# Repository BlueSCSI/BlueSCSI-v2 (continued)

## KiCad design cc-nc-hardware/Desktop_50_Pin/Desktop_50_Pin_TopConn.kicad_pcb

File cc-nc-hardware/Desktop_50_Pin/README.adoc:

BlueSCSI V2 Desktop 50 Pin
© 2022 - 2023 Tech by Androda, LLC

.All files in this cc-nc-hardware folder (and subfolders) are licensed CC BY-NC-SA 4.0:
* https://creativecommons.org/licenses/by-nc-sa/4.0/legalcode[Creative Commons Attribution-NonCommercial-ShareAlike 4.0 International Public License]

.The Dekstop 50 Pin hardware design contains one element which is © SnapEDA, as follows:
* SM04B-SRSS-TB(LF)(SN) Symbol And Footprint Copyright SnapEDA
* https://www.snapeda.com/parts/SM04B-SRSS-TB%28LF%29%28SN%29/JST%20Sales/view-part/
* License For This Symbol and Footprint Only: CC-BY-SA 4.0
* https://creativecommons.org/licenses/by-sa/4.0/
* This license contains a warranty disclaimer, please read it in full

.Translations of the CC BY-NC-SA 4.0 license are available, in a variety of languages:
* https://creativecommons.org/licenses/by-nc-sa/4.0/legalcode.fr[français]
* https://creativecommons.org/licenses/by-nc-sa/4.0/legalcode.ja[日本語]
* https://creativecommons.org/licenses/by-nc-sa/4.0/legalcode.pl[polski]
* https://creativecommons.org/licenses/by-nc-sa/4.0/legalcode.zh-Hans[中文]

.Explanations of the various rights afforded by this CC BY-NC-SA 4.0 license are also available in many languages:
* https://creativecommons.org/licenses/by-nc-sa/4.0/[English]
* https://creativecommons.org/licenses/by-nc-sa/4.0/deed.fr[français]
* https://creativecommons.org/licenses/by-nc-sa/4.0/deed.ja[日本語]
* https://creativecommons.org/licenses/by-nc-sa/4.0/deed.pl[polski]
* https://creativecommons.org/licenses/by-nc-sa/4.0/deed.zh[中文]

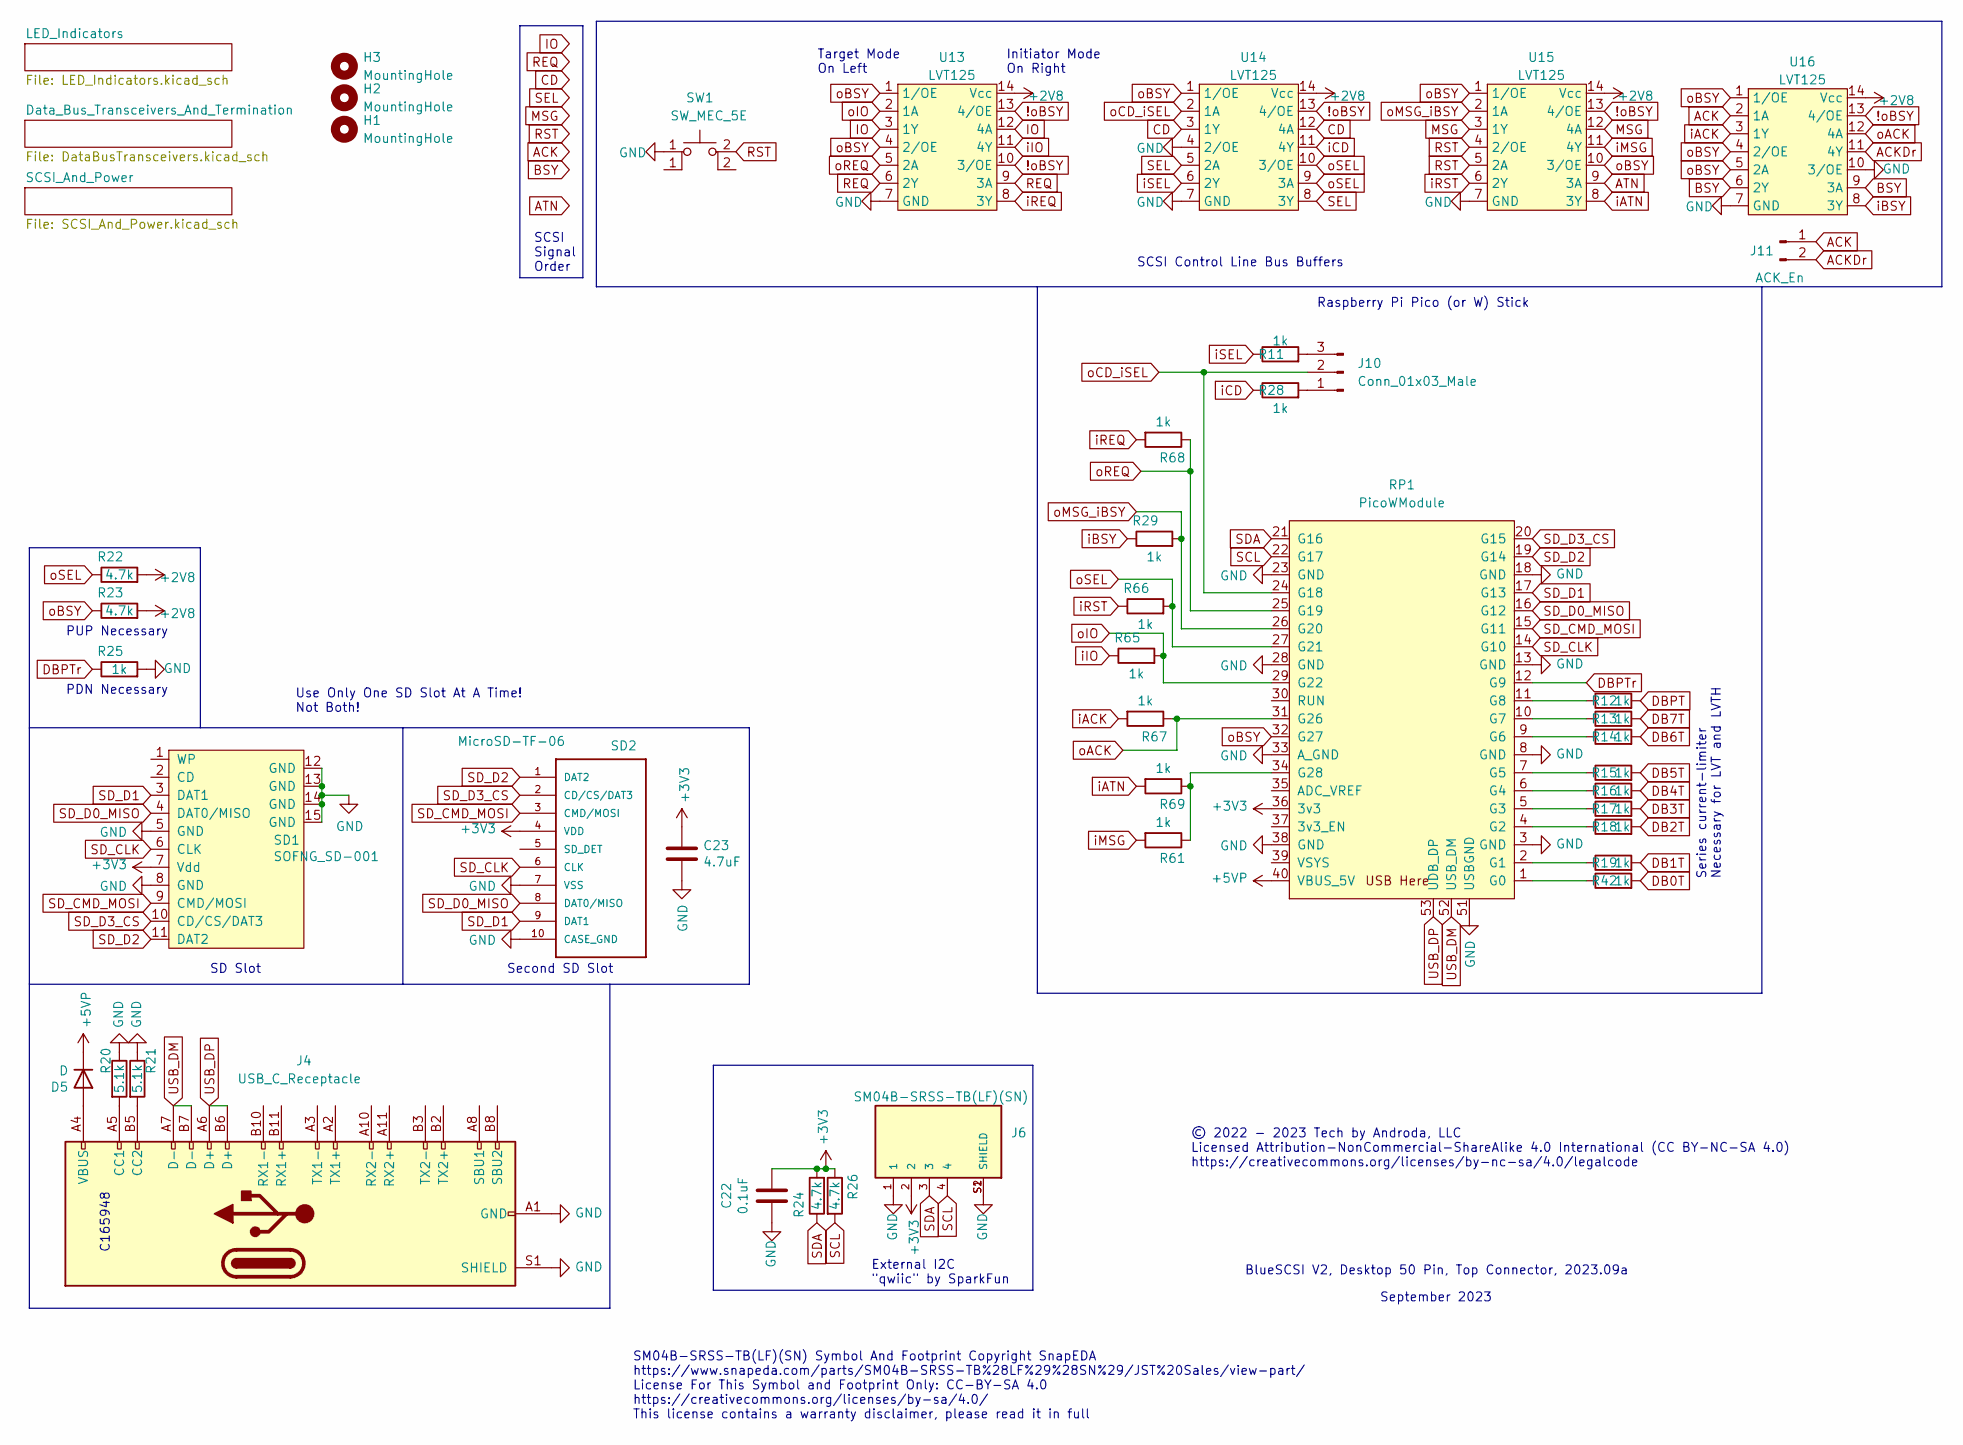
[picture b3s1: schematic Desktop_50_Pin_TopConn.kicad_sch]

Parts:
C22: 0.1uF; C_0805_2012Metric_Pad1.18x1.45mm_HandSolder
C23: 4.7uF; C_0805_2012Metric_Pad1.18x1.45mm_HandSolder
D5: D; D_SMA
H1, H2, H3: MountingHole; MountingHole_3.2mm_M3
J4: USB_C_Receptacle; USB_C_Receptacle_HRO_TYPE-C-31-M-12
J6: SM04B-SRSS-TB(LF)(SN); JST_SM04B-SRSS-TB(LF)(SN)
J10: Conn_01x03_Male; PinHeader_1x03_P2.54mm_Vertical
J11: ACK_En; PinHeader_1x02_P2.54mm_Vertical
R11, R25, R28, R29, R61, R65, R66, R67, R68, R69: 1k; R_0402_1005Metric
R12, R13, R14, R15, R16, R17, R18, R19, R42: 1k; R_0402_1005Metric_Pad0.72x0.64mm_HandSolder
R20, R21: 5.1k; R_0402_1005Metric
R22, R23, R24, R26: 4.7k; R_0603_1608Metric
RP1: PicoWModule; Raspberry_Pi_PicoW_SMT_THT
SD1: SOFNG_SD-001
SD2: MicroSD-TF-06; TF-06_MicroSD; MANUFACTURER_PART_NUMBER C693844
SW1: SW_MEC_5E; TS-1187A-B-A-B
U13, U14, U15, U16: LVT125; TSSOP-14_4.4x5mm_P0.65mm

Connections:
!oBSY: U13.10 (3/OE), U13.13 (4/OE), U14.13 (4/OE), U15.13 (4/OE), U16.13 (4/OE); also elsewhere on the board
+2V8: R22.2, R23.2, U13.14 (Vcc), U14.14 (Vcc), U15.14 (Vcc), U16.14 (Vcc); also elsewhere on the board
ACK: J11.1, U16.2 (1A); also elsewhere on the board
ACKDr: J11.2, U16.11 (4Y)
ATN: U15.9 (3A); also elsewhere on the board
BSY: U16.6 (2Y), U16.9 (3A); also elsewhere on the board
CD: U14.3 (1Y), U14.12 (4A); also elsewhere on the board
DB0T: R42.2; also elsewhere on the board
DB1T: R19.2; also elsewhere on the board
DB2T: R18.2; also elsewhere on the board
DB3T: R17.2; also elsewhere on the board
DB4T: R16.2; also elsewhere on the board
DB5T: R15.2; also elsewhere on the board
DB6T: R14.2; also elsewhere on the board
DB7T: R13.2; also elsewhere on the board
DBPT: R12.2; also elsewhere on the board
DBPTr: R25.1, RP1.12 (G9); also elsewhere on the board
GND: C22.1, C23.2, J4.A1 (GND), J4.A12 (GND), J4.B1 (GND), J4.B12 (GND), J4.S1 (SHIELD), J6.1, J6.S1 (SHIELD), J6.S2 (SHIELD), R20.1, R21.1, R25.2, RP1.3 (GND), RP1.8 (GND), RP1.13 (GND), RP1.18 (GND), RP1.23 (GND), RP1.28 (GND), RP1.33 (A_GND), RP1.38 (GND), RP1.51 (USBGND), SD1.5 (GND), SD1.8 (GND), SD1.12 (GND), SD1.13 (GND), SD1.14 (GND), SD1.15 (GND), SD2.7 (VSS), SD2.10 (CASE_GND), SW1.1, U13.7 (GND), U14.4 (2/OE), U14.7 (GND), U15.7 (GND), U16.7 (GND), U16.10 (3/OE); also elsewhere on the board
IO: U13.3 (1Y), U13.12 (4A); also elsewhere on the board
MSG: U15.3 (1Y), U15.12 (4A); also elsewhere on the board
unnamed: D5.2 (A), J4.A4 (VBUS), J4.A9 (VBUS), J4.B4 (VBUS), J4.B9 (VBUS)
unnamed: J4.A5 (CC1), R20.2
unnamed: J4.B5 (CC2), R21.2
unnamed: J10.1, R28.2
unnamed: J10.3, R11.2
unnamed: R12.1, RP1.11 (G8)
unnamed: R13.1, RP1.10 (G7)
unnamed: R14.1, RP1.9 (G6)
unnamed: R15.1, RP1.7 (G5)
unnamed: R16.1, RP1.6 (G4)
unnamed: R17.1, RP1.5 (G3)
unnamed: R18.1, RP1.4 (G2)
unnamed: R19.1, RP1.2 (G1)
unnamed: R42.1, RP1.1 (G0)
unnamed: R61.1, R69.1, RP1.34 (G28)
REQ: U13.6 (2Y), U13.9 (3A); also elsewhere on the board
RST: SW1.2 (A), U15.4 (2/OE), U15.5 (2A); also elsewhere on the board
SCL: J6.4, R26.2, RP1.22 (G17)
SDA: J6.3, R24.1, RP1.21 (G16)
SD_CLK: RP1.14 (G10), SD1.6 (CLK), SD2.6 (CLK)
SD_CMD_MOSI: RP1.15 (G11), SD1.9 (CMD/MOSI), SD2.3 (CMD/MOSI)
SD_D0_MISO: RP1.16 (G12), SD1.4 (DAT0/MISO), SD2.8 (DAT0/MISO)
SD_D1: RP1.17 (G13), SD1.3 (DAT1), SD2.9 (DAT1)
SD_D2: RP1.19 (G14), SD1.11 (DAT2), SD2.1 (DAT2)
SD_D3_CS: RP1.20 (G15), SD1.10 (CD/CS/DAT3), SD2.2 (CD/CS/DAT3)
SEL: U14.5 (2A), U14.8 (3Y); also elsewhere on the board
USB_DM: J4.A7 (D-), J4.B7 (D-), RP1.52 (USB_DM)
USB_DP: J4.A6 (D+), J4.B6 (D+), RP1.53 (UDB_DP)
iACK: R67.2, U16.3 (1Y)
iATN: R69.2, U15.8 (3Y)
iBSY: R29.1, U16.8 (3Y)
iCD: R28.1, U14.11 (4Y)
iIO: R65.1, U13.11 (4Y)
iMSG: R61.2, U15.11 (4Y)
iREQ: R68.2, U13.8 (3Y)
iRST: R66.1, U15.6 (2Y)
iSEL: R11.1, U14.6 (2Y)
oACK: R67.1, RP1.31 (G26), U16.12 (4A)
oBSY: R23.1, RP1.32 (G27), U13.1 (1/OE), U13.4 (2/OE), U14.1 (1/OE), U15.1 (1/OE), U15.10 (3/OE), U16.1 (1/OE), U16.4 (2/OE), U16.5 (2A); also elsewhere on the board
oCD_iSEL: J10.2, RP1.24 (G18), U14.2 (1A)
oIO: R65.2, RP1.29 (G22), U13.2 (1A)
oMSG_iBSY: R29.2, RP1.26 (G20), U15.2 (1A)
oREQ: R68.1, RP1.25 (G19), U13.5 (2A)
oSEL: R22.1, R66.2, RP1.27 (G21), U14.9 (3A), U14.10 (3/OE)

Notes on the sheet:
Use Only One SD Slot At A Time! Not Both!
Series current-limiter Necessary for LVT and LVTH
Second SD Slot
C165948
© 2022 - 2023 Tech by Androda, LLC Licensed Attribution-NonCommercial-ShareAlike 4.0 International (CC BY-NC-SA 4.0) https://creativecommons.org/licenses/by-nc-sa/4.0/legalcode
September 2023
Target Mode On Left
SCSI Control Line Bus Buffers
Initiator Mode On Right
SM04B-SRSS-TB(LF)(SN) Symbol And Footprint Copyright SnapEDA https://www.snapeda.com/parts/SM04B-SRSS-TB%28LF%29%28SN%29/JST%20Sales/view-part/ License For This Symbol and Footprint Only: CC-BY-SA 4.0 https://creativecommons.org/licenses/by-sa/4.0/ This license contains a warranty disclaimer, pleas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
BlueSCSI V2, Desktop 50 Pin, Top Connector, 2023.09a
External I2C "qwiic" by SparkFun
SCSI Signal Order
SD Slot
PUP Necessary
PDN Necessary
Raspberry Pi Pico (or W) Stick

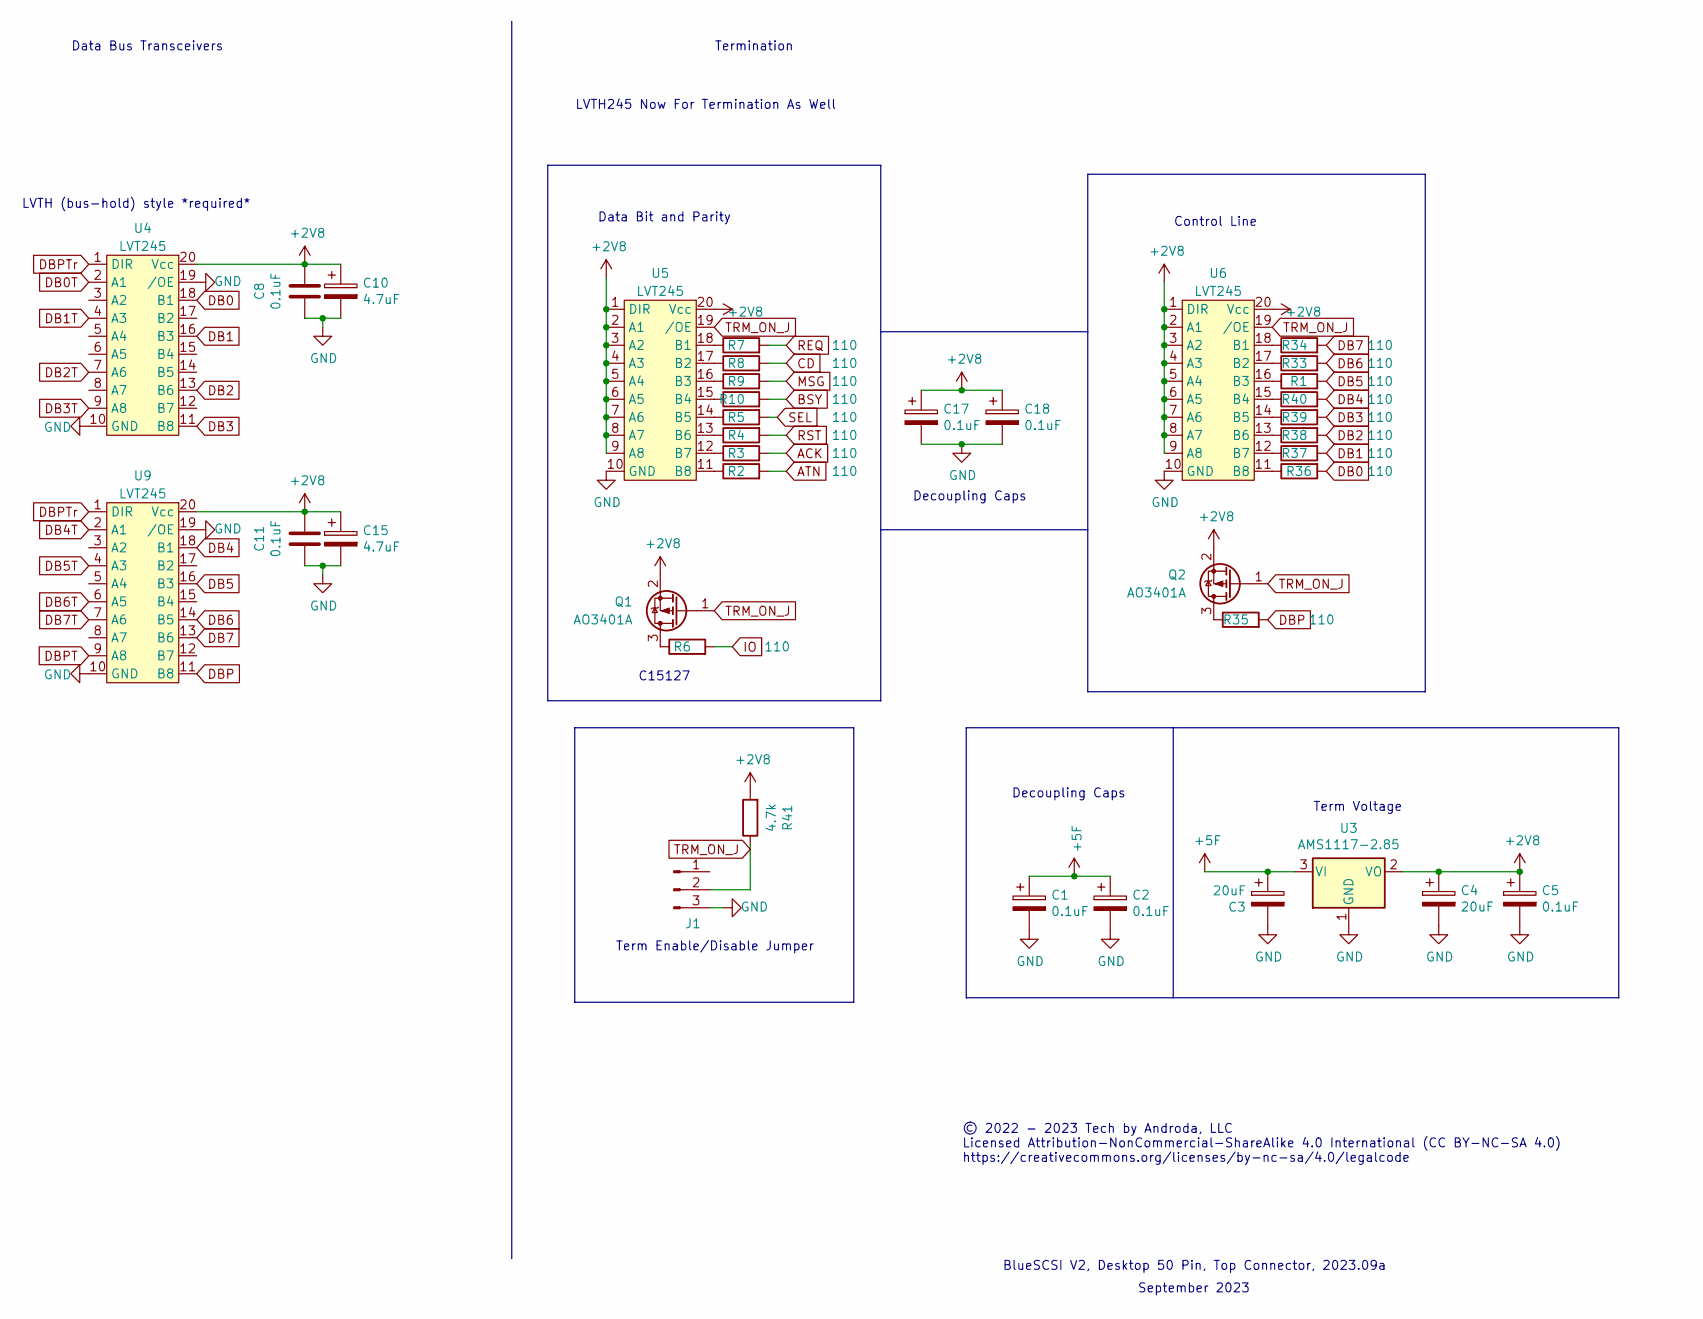
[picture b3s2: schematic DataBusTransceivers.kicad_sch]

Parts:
C1, C2, C5: 0.1uF; C_0805_2012Metric_Pad1.15x1.40mm_HandSolder
C3, C4: 20uF; C_1206_3216Metric_Pad1.42x1.75mm_HandSolder
C8, C11: 0.1uF; C_0805_2012Metric_Pad1.18x1.45mm_HandSolder
C10, C15: 4.7uF; C_0805_2012Metric_Pad1.18x1.45mm_HandSolder
C17, C18: 0.1uF; C_0805_2012Metric
J1: Conn_01x03_Male; PinHeader_1x03_P2.54mm_Vertical
Q1, Q2: AO3401A; SOT-23
R1, R2, R3, R4, R5, R6, R7, R8, R9, R10, R33, R34, R35, R36, R37, R38, R39, R40: 110; R_0603_1608Metric_Pad0.98x0.95mm_HandSolder
R41: 4.7k; R_0603_1608Metric_Pad0.98x0.95mm_HandSolder
U3: AMS1117-2.85; SOT-223-3_TabPin2
U4, U5, U6, U9: LVT245; TSSOP-20_4.4x6.5mm_P0.65mm

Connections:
+2V8: C4.1, C5.1, C8.1, C10.1, C11.1, C15.1, C17.1, C18.1, Q1.2 (S), Q2.2 (S), R41.2, U3.2 (VO), U4.20 (Vcc), U5.1 (DIR), U5.2 (A1), U5.3 (A2), U5.4 (A3), U5.5 (A4), U5.6 (A5), U5.7 (A6), U5.8 (A7), U5.9 (A8), U5.20 (Vcc), U6.1 (DIR), U6.2 (A1), U6.3 (A2), U6.4 (A3), U6.5 (A4), U6.6 (A5), U6.7 (A6), U6.8 (A7), U6.9 (A8), U6.20 (Vcc), U9.20 (Vcc); also elsewhere on the board
+5F: C1.1, C2.1, C3.1, U3.3 (VI); also elsewhere on the board
ACK: R3.2; also elsewhere on the board
ATN: R2.2; also elsewhere on the board
BSY: R10.2; also elsewhere on the board
CD: R8.2; also elsewhere on the board
DB0: R36.2, U4.18 (B1); also elsewhere on the board
DB0T: U4.2 (A1); also elsewhere on the board
DB1: R37.2, U4.16 (B3); also elsewhere on the board
DB1T: U4.4 (A3); also elsewhere on the board
DB2: R38.2, U4.13 (B6); also elsewhere on the board
DB2T: U4.7 (A6); also elsewhere on the board
DB3: R39.2, U4.11 (B8); also elsewhere on the board
DB3T: U4.9 (A8); also elsewhere on the board
DB4: R40.2, U9.18 (B1); also elsewhere on the board
DB4T: U9.2 (A1); also elsewhere on the board
DB5: R1.2, U9.16 (B3); also elsewhere on the board
DB5T: U9.4 (A3); also elsewhere on the board
DB6: R33.2, U9.14 (B5); also elsewhere on the board
DB6T: U9.6 (A5); also elsewhere on the board
DB7: R34.2, U9.13 (B6); also elsewhere on the board
DB7T: U9.7 (A6); also elsewhere on the board
DBP: R35.2, U9.11 (B8); also elsewhere on the board
DBPT: U9.9 (A8); also elsewhere on the board
DBPTr: U4.1 (DIR), U9.1 (DIR); also elsewhere on the board
GND: C1.2, C2.2, C3.2, C4.2, C5.2, C8.2, C10.2, C11.2, C15.2, C17.2, C18.2, J1.3, U3.1 (GND), U4.10 (GND), U4.19 (/OE), U5.10 (GND), U6.10 (GND), U9.10 (GND), U9.19 (/OE); also elsewhere on the board
IO: R6.2; also elsewhere on the board
MSG: R9.2; also elsewhere on the board
unnamed: Q1.3 (D), R6.1
unnamed: Q2.3 (D), R35.1
unnamed: R1.1, U6.16 (B3)
unnamed: R2.1, U5.11 (B8)
unnamed: R3.1, U5.12 (B7)
unnamed: R4.1, U5.13 (B6)
unnamed: R5.1, U5.14 (B5)
unnamed: R7.1, U5.18 (B1)
unnamed: R8.1, U5.17 (B2)
unnamed: R9.1, U5.16 (B3)
unnamed: R10.1, U5.15 (B4)
unnamed: R33.1, U6.17 (B2)
unnamed: R34.1, U6.18 (B1)
unnamed: R36.1, U6.11 (B8)
unnamed: R37.1, U6.12 (B7)
unnamed: R38.1, U6.13 (B6)
unnamed: R39.1, U6.14 (B5)
unnamed: R40.1, U6.15 (B4)
REQ: R7.2; also elsewhere on the board
RST: R4.2; also elsewhere on the board
SEL: R5.2; also elsewhere on the board
TRM_ON_J: J1.2, Q1.1 (G), Q2.1 (G), R41.1, U5.19 (/OE), U6.19 (/OE)

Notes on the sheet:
Data Bus Transceivers
C15127
Control Line
Decoupling Caps
Data Bit and Parity
© 2022 - 2023 Tech by Androda, LLC Licensed Attribution-NonCommercial-ShareAlike 4.0 International (CC BY-NC-SA 4.0) https://creativecommons.org/licenses/by-nc-sa/4.0/legalcode
BlueSCSI V2, Desktop 50 Pin, Top Connector, 2023.09a
Termination
Term Voltage
Term Enable/Disable Jumper
September 2023
LVTH245 Now For Termination As Well
LVTH (bus-hold) style *required*

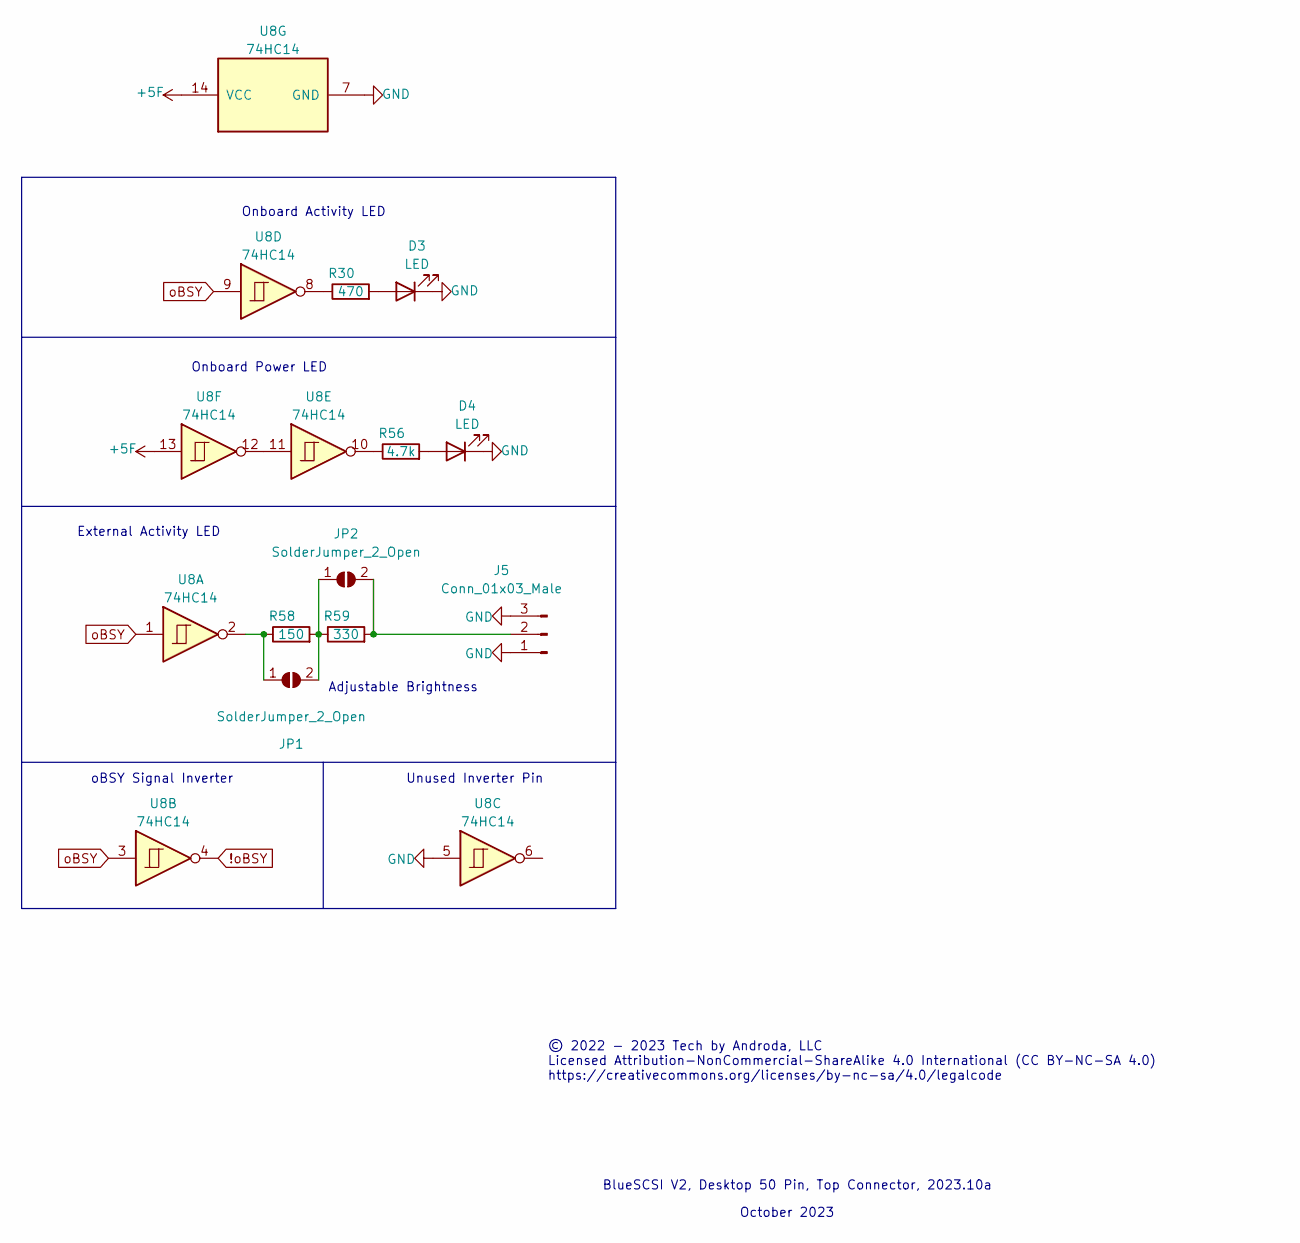
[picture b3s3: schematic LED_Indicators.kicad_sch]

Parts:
D3: LED; LED_0603_1608Metric_Pad1.05x0.95mm_HandSolder; JLCPCB Part Number C72041
D4: LED; LED_0603_1608Metric_Pad1.05x0.95mm_HandSolder; JLCPCB Part # C2290
J5: Conn_01x03_Male; PinHeader_1x03_P2.54mm_Vertical
JP1, JP2: SolderJumper_2_Open; SolderJumper-2_P1.3mm_Open_RoundedPad1.0x1.5mm
R30: 470; R_0402_1005Metric_Pad0.72x0.64mm_HandSolder
R56: 4.7k; R_0603_1608Metric_Pad0.98x0.95mm_HandSolder
R58: 150; R_0603_1608Metric_Pad0.98x0.95mm_HandSolder
R59: 330; R_0603_1608Metric_Pad0.98x0.95mm_HandSolder
U8: 74HC14

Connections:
!oBSY: U8.4; also elsewhere on the board
+5F: U8.13, U8.14 (VCC); also elsewhere on the board
GND: D3.1 (K), D4.1 (K), J5.1, J5.3, U8.5, U8.7 (GND); also elsewhere on the board
unnamed: D3.2 (A), R30.2
unnamed: D4.2 (A), R56.2
unnamed: J5.2, JP2.2 (B), R59.2
unnamed: JP1.1 (A), R58.1, U8.2
unnamed: JP1.2 (B), JP2.1 (A), R58.2, R59.1
unnamed: R30.1, U8.8
unnamed: R56.1, U8.10
unnamed: U8.11, U8.12
oBSY: U8.1, U8.3, U8.9; also elsewhere on the board

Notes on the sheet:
Onboard Power LED
Unused Inverter Pin
oBSY Signal Inverter
© 2022 - 2023 Tech by Androda, LLC Licensed Attribution-NonCommercial-ShareAlike 4.0 International (CC BY-NC-SA 4.0) https://creativecommons.org/licenses/by-nc-sa/4.0/legalcode
BlueSCSI V2, Desktop 50 Pin, Top Connector, 2023.10a
Onboard Activity LED
Adjustable Brightness
External Activity LED
October 2023

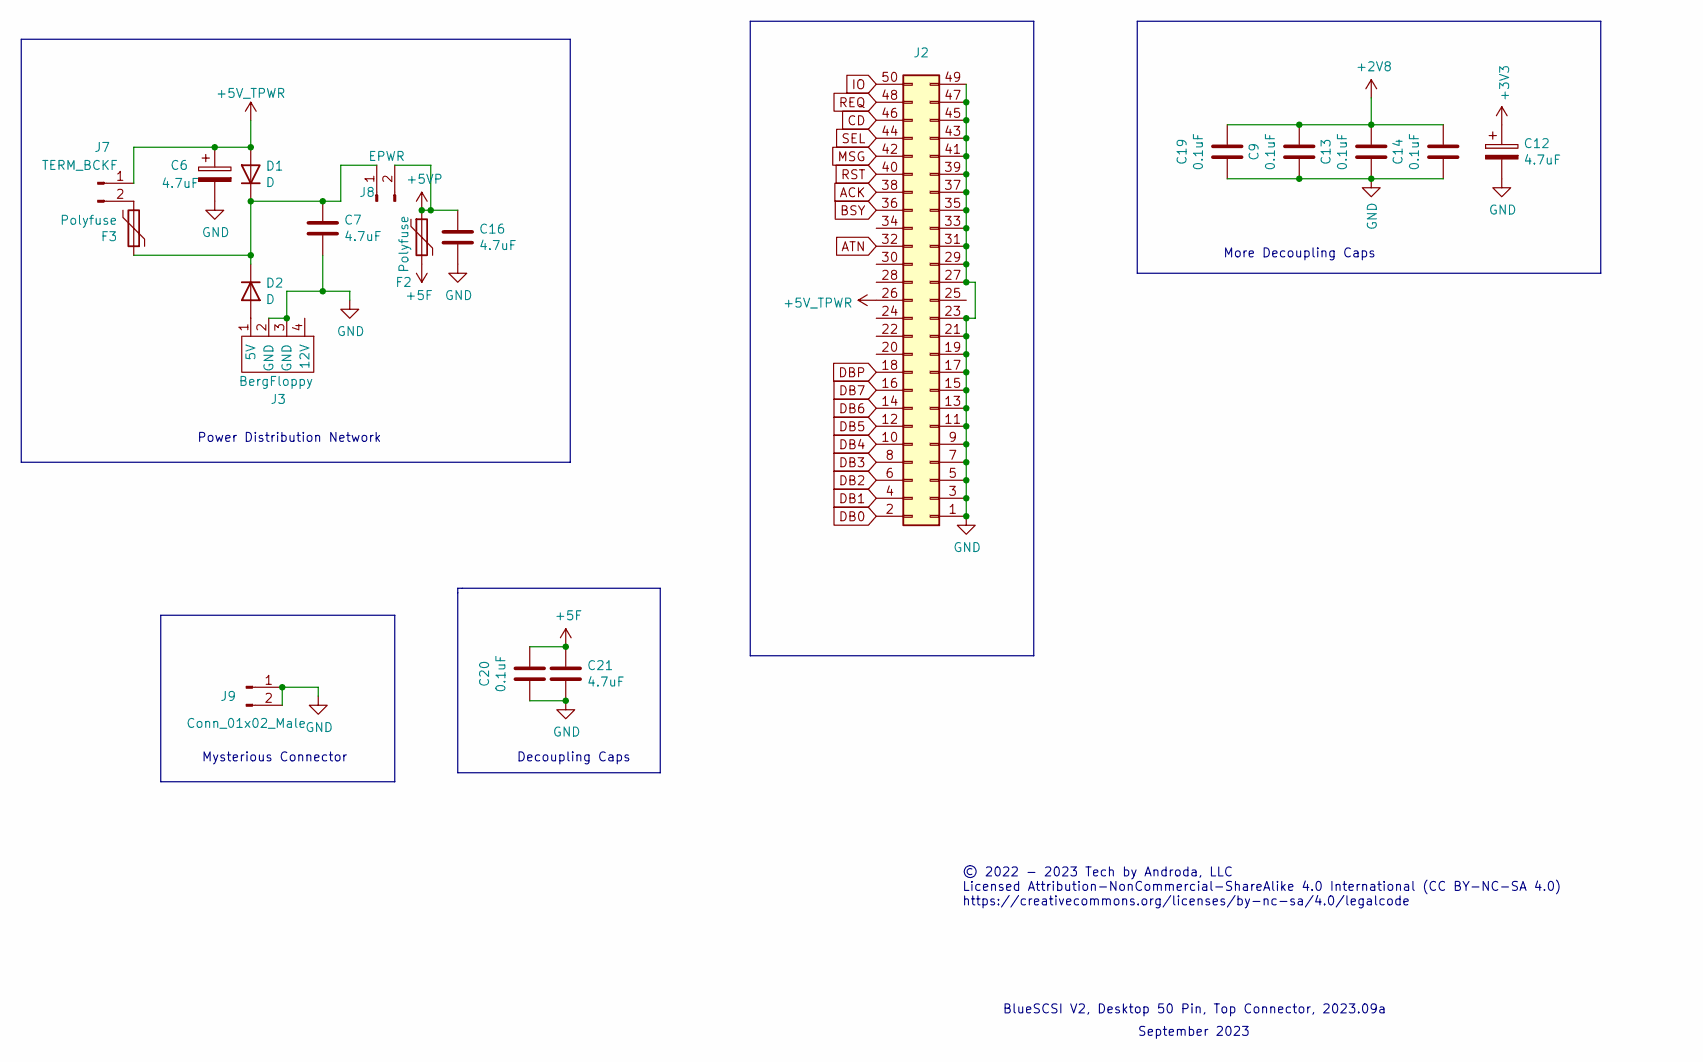
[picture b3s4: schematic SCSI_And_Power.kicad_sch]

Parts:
C6, C7, C12: 4.7uF; C_0805_2012Metric_Pad1.15x1.40mm_HandSolder
C9, C13, C14, C19, C20: 0.1uF; C_0805_2012Metric_Pad1.18x1.45mm_HandSolder
C16, C21: 4.7uF; C_0805_2012Metric_Pad1.18x1.45mm_HandSolder
D1, D2: D; D_SMA
F2: Polyfuse; Fuse_0805_2012Metric_Pad1.15x1.40mm_HandSolder
F3: Polyfuse; Fuse_0805_2012Metric_Pad1.15x1.40mm_HandSolder; JLC Part# C883109
J2: Conn_02x25_Odd_Even; PinHeader_2x25_P2.54mm_Horizontal
J3: BergFloppy; BergFloppy_RightAngle
J7: TERM_BCKF; PinHeader_1x02_P2.54mm_Vertical
J8: EPWR; PinHeader_1x02_P2.54mm_Vertical
J9: Conn_01x02_Male; PinHeader_1x02_P2.54mm_Vertical

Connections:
+2V8: C9.2, C13.2, C14.2, C19.2; also elsewhere on the board
+5F: C20.2, C21.1, F2.2; also elsewhere on the board
+5V: C6.1, D1.2 (A), J2.26, J7.1
ACK: J2.38; also elsewhere on the board
ATN: J2.32; also elsewhere on the board
BSY: J2.36; also elsewhere on the board
CD: J2.46; also elsewhere on the board
DB0: J2.2; also elsewhere on the board
DB1: J2.4; also elsewhere on the board
DB2: J2.6; also elsewhere on the board
DB3: J2.8; also elsewhere on the board
DB4: J2.10; also elsewhere on the board
DB5: J2.12; also elsewhere on the board
DB6: J2.14; also elsewhere on the board
DB7: J2.16; also elsewhere on the board
DBP: J2.18; also elsewhere on the board
GND: C6.2, C7.2, C9.1, C12.2, C13.1, C14.1, C16.2, C19.1, C20.1, C21.2, J2.1, J2.3, J2.5, J2.7, J2.9, J2.11, J2.13, J2.15, J2.17, J2.19, J2.21, J2.23, J2.27, J2.29, J2.31, J2.33, J2.35, J2.37, J2.39, J2.41, J2.43, J2.45, J2.47, J2.49, J3.2 (GND), J3.3 (GND), J9.1, J9.2; also elsewhere on the board
IO: J2.50; also elsewhere on the board
MSG: J2.42; also elsewhere on the board
unnamed: C7.1, D1.1 (K), D2.1 (K), F3.1, J8.1
unnamed: D2.2 (A), J3.1 (5V)
unnamed: F3.2, J7.2
REQ: J2.48; also elsewhere on the board
RST: J2.40; also elsewhere on the board
SEL: J2.44; also elsewhere on the board

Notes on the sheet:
Decoupling Caps
Power Distribution Network
Mysterious Connector
More Decoupling Caps
September 2023
© 2022 - 2023 Tech by Androda, LLC Licensed Attribution-NonCommercial-ShareAlike 4.0 International (CC BY-NC-SA 4.0) https://creativecommons.org/licenses/by-nc-sa/4.0/legalcode
BlueSCSI V2, Desktop 50 Pin, Top Connector, 2023.09a

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
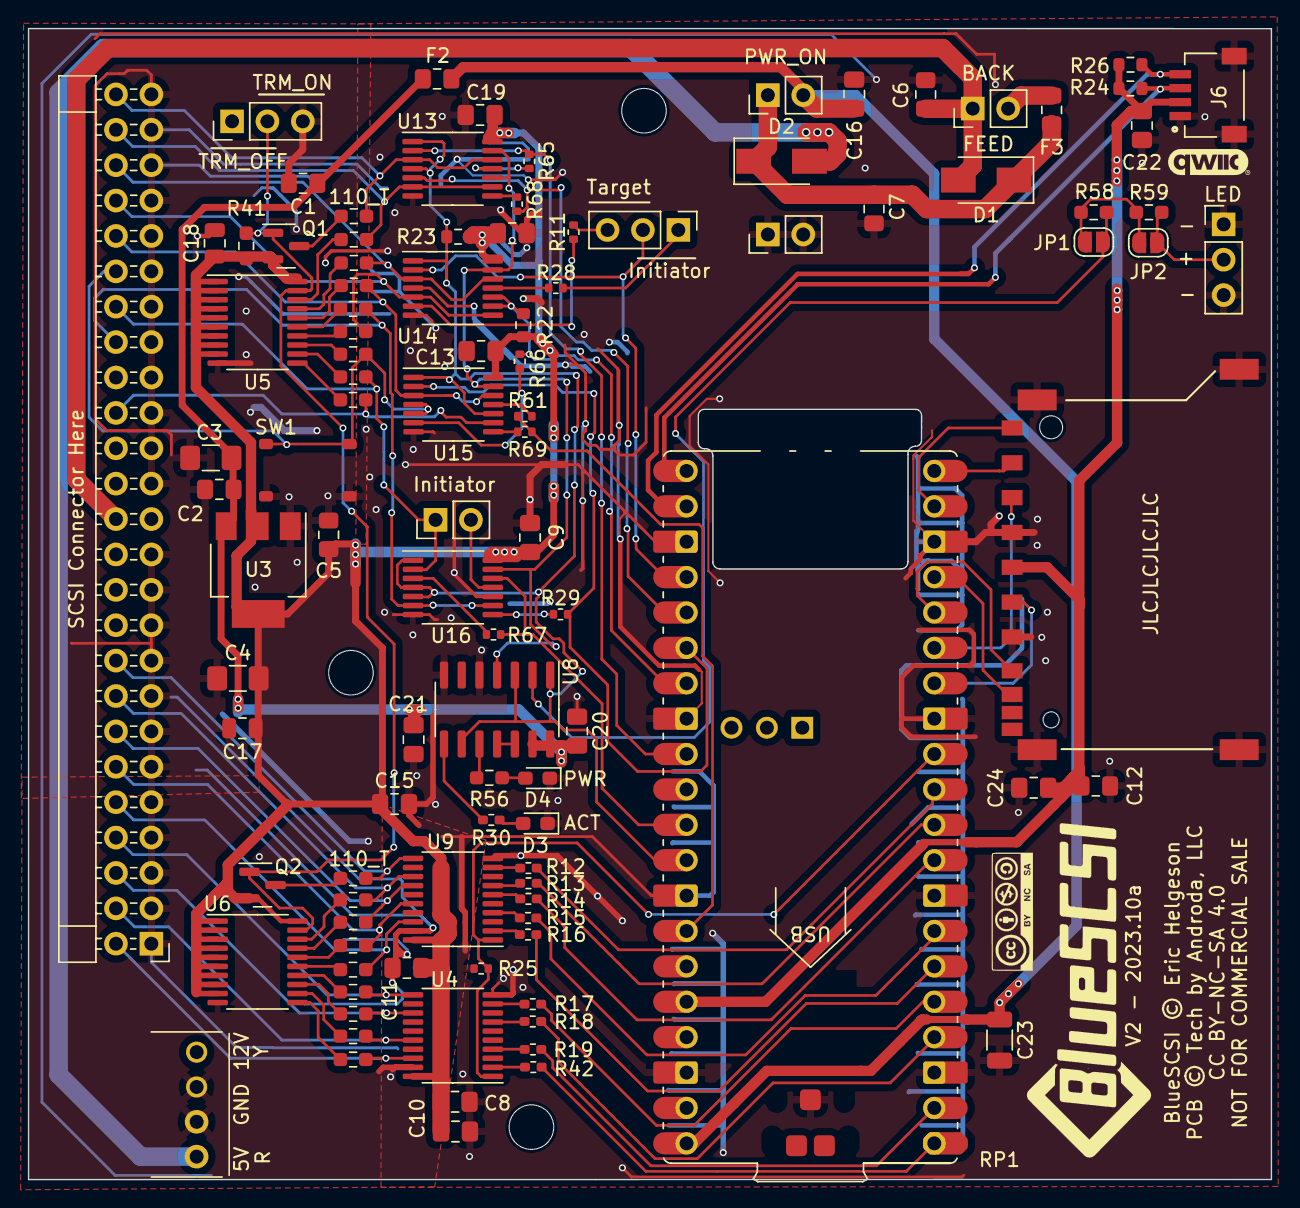
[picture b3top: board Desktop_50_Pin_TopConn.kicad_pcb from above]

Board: 2 copper layers, 89.2 x 82.6 mm, 106 parts (0 on the bottom side), 102 nets.

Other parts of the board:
C24: 0.1uF; C_0805_2012Metric_Pad1.18x1.45mm_HandSolder

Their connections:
GND: C24.2; also elsewhere on the board

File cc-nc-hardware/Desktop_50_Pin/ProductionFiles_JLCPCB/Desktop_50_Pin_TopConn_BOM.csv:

Comment,Designator,Footprint,LCSC Part Number
4.7uF,"C23,C16,C15,C10,C21,C7,C6,C12",C_0805_2012Metric_Pad1.18x1.45mm_HandSolder,C1779
20uF,"C3,C4",C_1206_3216Metric_Pad1.42x1.75mm_HandSolder,C5672
AMS1117-2.85,U3,SOT-223-3_TabPin2,C14791
0.1uF,"C1,C2,C5,C17,C18,C8,C19,C14,C20,C22,C9,C11,C13",C_0805_2012Metric_Pad1.15x1.40mm_HandSolder,C28233
SOFNG_SD-001,SD1,SOFNG_SD-001,C428452
D,"D1,D2,D5",D_SMA,C2480
1k,"R42,R16,R17,R13,R18,R15,R12,R19,R14,R66,R67,R11,R69,R68,R65,R29,R28,R61,R25",R_0402_1005Metric_Pad0.72x0.64mm_HandSolder,C11702
4.7k,"R56,R41,R24,R22,R26,R23",R_0603_1608Metric_Pad0.98x0.95mm_HandSolder,C23162
AO3401A,"Q1,Q2",SOT-23,C15127
110,"R39,R4,R33,R36,R5,R35,R1,R38,R9,R40,R3,R7,R8,R2,R10,R34,R37,R6",R_0603_1608Metric_Pad0.98x0.95mm_HandSolder,C141676
LVT245,"U5,U4,U6,U9",TSSOP-20_4.4x6.5mm_P0.65mm,C2652121
LVT125,"U14,U13,U16,U15",TSSOP-14_4.4x5mm_P0.65mm,C7042
USB_C_Receptacle,J4,USB_C_Receptacle_HRO_TYPE-C-31-M-12,C165948
Polyfuse,"F3,F2",Fuse_0805_2012Metric_Pad1.15x1.40mm_HandSolder,C883111
330,R59,R_0603_1608Metric_Pad0.98x0.95mm_HandSolder,C23138
MicroSD-TF-06,SD2,TF-06_MicroSD,C693844
5.1k,"R21,R20",R_0402_1005Metric,C25905
LED PWR,D4,LED_0603_1608Metric_Pad1.05x0.95mm_HandSolder,C2290
LED ACT,D3,LED_0603_1608Metric_Pad1.05x0.95mm_HandSolder,C72041
SW_MEC_5E,SW1,TS-1187A-B-A-B,C318884
74HC14,U8,SO-14_3.9x8.65mm_P1.27mm,C5605
SM04B-SRSS-TB(LF)(SN),J6,JST_SM04B-SRSS-TB(LF)(SN),C160404
150,R58,R_0603_1608Metric_Pad0.98x0.95mm_HandSolder,C22808
0402WGF4700TCE,R30,402,C25117

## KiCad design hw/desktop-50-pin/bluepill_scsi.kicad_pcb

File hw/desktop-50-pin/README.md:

BlueSCSI Hardware © 2021 by Eric Helgeson is licensed under Attribution-NonCommercial 4.0 International

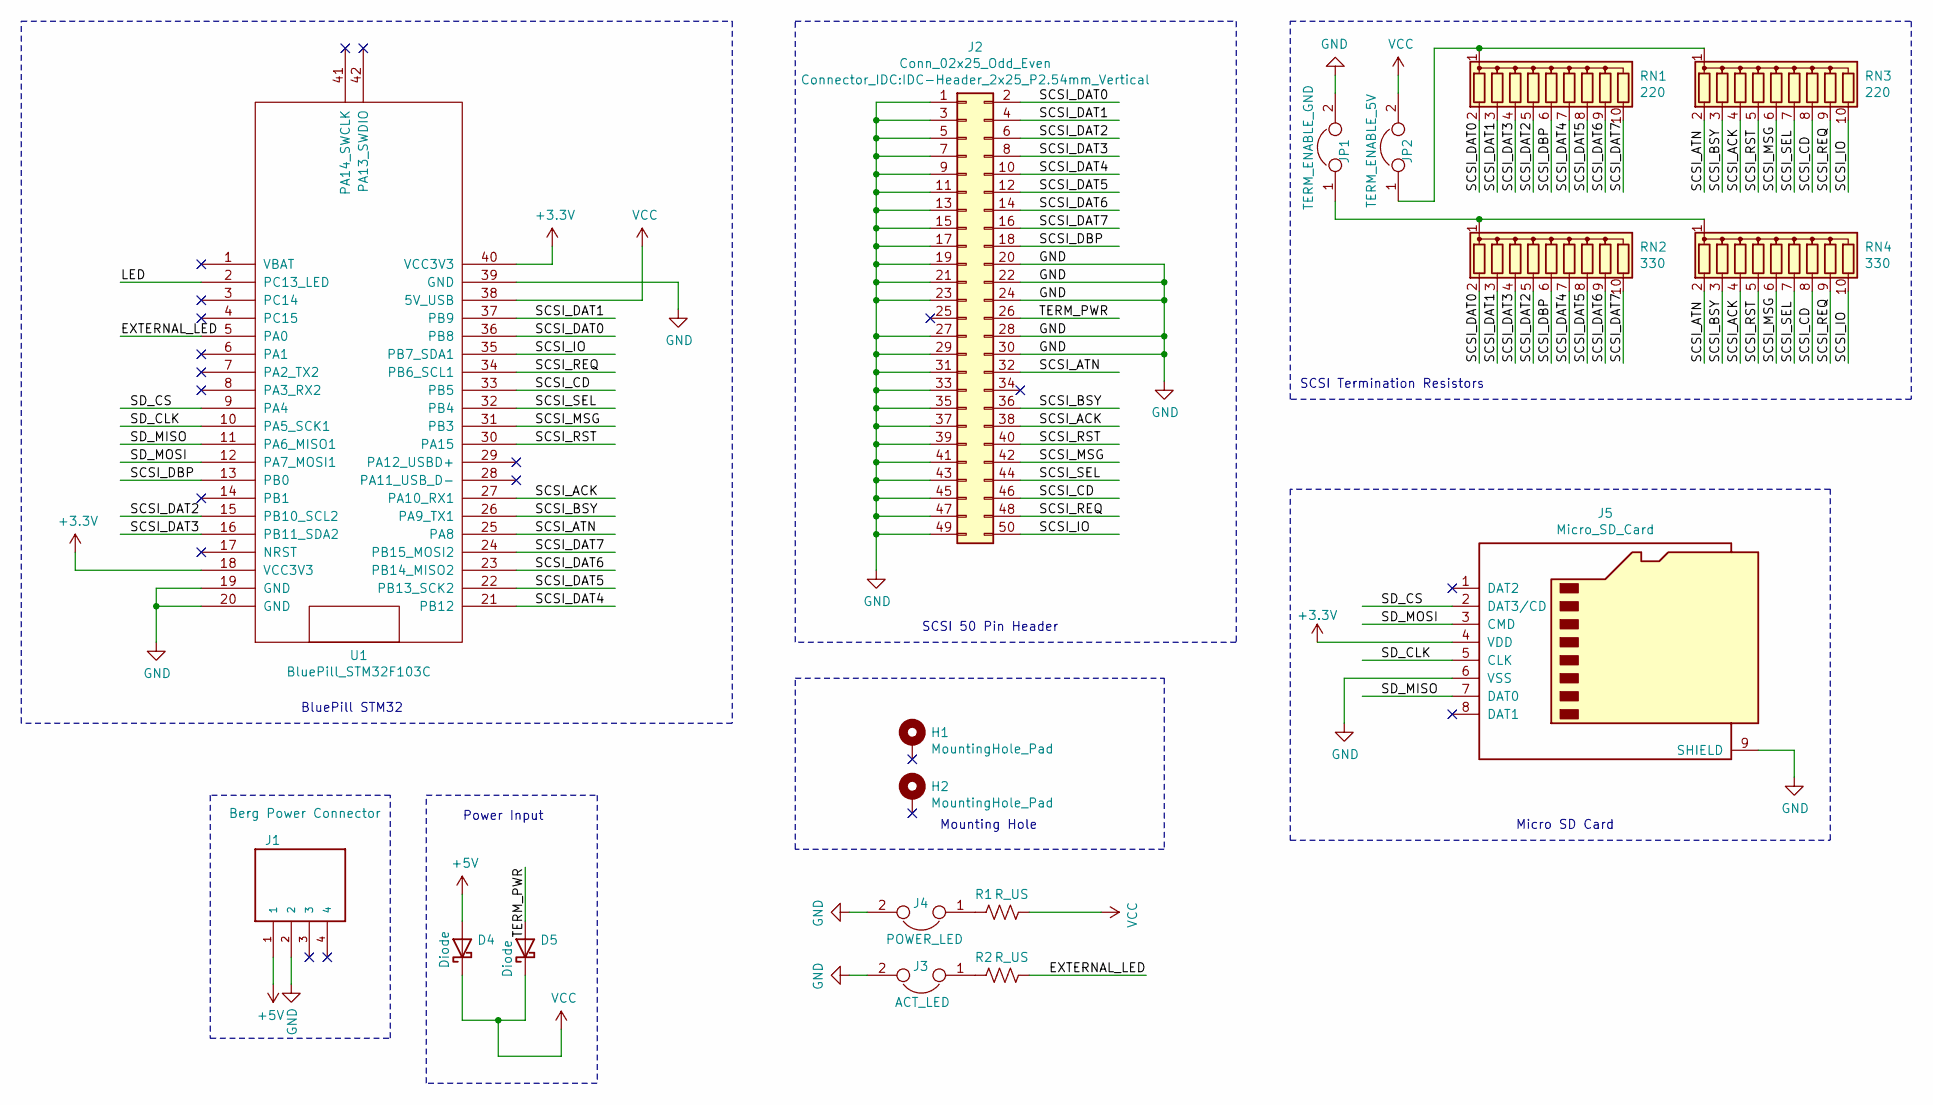
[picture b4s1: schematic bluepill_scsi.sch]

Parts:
D4, D5: Diode; D_A-405_P7.62mm_Horizontal
H1, H2: MountingHole_Pad; MountingHole_2.7mm_M2.5_Pad_Via
J1: Berg Power Connector; TE_171825-4
J2: Conn_02x25_Odd_Even; IDC-Header_2x25_P2.54mm_Vertical
J3: ACT_LED; PinSocket_1x02_P2.54mm_Vertical
J4: POWER_LED; PinSocket_1x02_P2.54mm_Vertical
J5: Micro_SD_Card; microSD_HC_Molex_104031-0811
JP1: TERM_ENABLE_GND; PinSocket_1x02_P2.54mm_Vertical
JP2: TERM_ENABLE_5V; PinSocket_1x02_P2.54mm_Vertical
R1, R2: R_US; R_Axial_DIN0204_L3.6mm_D1.6mm_P5.08mm_Horizontal
RN1, RN3: 220; R_Array_SIP10
RN2, RN4: 330; R_Array_SIP10
U1: BluePill_STM32F103C

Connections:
+3V3: J5.4 (VDD), U1.18 (VCC3V3), U1.40 (VCC3V3)
+5V: D4.2 (A), J1.1
/EXTERNAL_LED: R2.2, U1.5 (PA0)
/SCSI_ACK: J2.38, RN3.4 (R3), RN4.4 (R3), U1.27 (PA10_RX1)
/SCSI_ATN: J2.32, RN3.2 (R1), RN4.2 (R1), U1.25 (PA8)
/SCSI_BSY: J2.36, RN3.3 (R2), RN4.3 (R2), U1.26 (PA9_TX1)
/SCSI_CD: J2.46, RN3.8 (R7), RN4.8 (R7), U1.33 (PB5)
/SCSI_DAT0: J2.2, RN1.2 (R1), RN2.2 (R1), U1.36 (PB8)
/SCSI_DAT1: J2.4, RN1.3 (R2), RN2.3 (R2), U1.37 (PB9)
/SCSI_DAT2: J2.6, RN1.5 (R4), RN2.5 (R4), U1.15 (PB10_SCL2)
/SCSI_DAT3: J2.8, RN1.4 (R3), RN2.4 (R3), U1.16 (PB11_SDA2)
/SCSI_DAT4: J2.10, RN1.7 (R6), RN2.7 (R6), U1.21 (PB12)
/SCSI_DAT5: J2.12, RN1.8 (R7), RN2.8 (R7), U1.22 (PB13_SCK2)
/SCSI_DAT6: J2.14, RN1.9 (R8), RN2.9 (R8), U1.23 (PB14_MISO2)
/SCSI_DAT7: J2.16, RN1.10 (R9), RN2.10 (R9), U1.24 (PB15_MOSI2)
/SCSI_DBP: J2.18, RN1.6 (R5), RN2.6 (R5), U1.13 (PB0)
/SCSI_IO: J2.50, RN3.10 (R9), RN4.10 (R9), U1.35 (PB7_SDA1)
/SCSI_MSG: J2.42, RN3.6 (R5), RN4.6 (R5), U1.31 (PB3)
/SCSI_REQ: J2.48, RN3.9 (R8), RN4.9 (R8), U1.34 (PB6_SCL1)
/SCSI_RST: J2.40, RN3.5 (R4), RN4.5 (R4), U1.30 (PA15)
/SCSI_SEL: J2.44, RN3.7 (R6), RN4.7 (R6), U1.32 (PB4)
/SD_CLK: J5.5 (CLK), U1.10 (PA5_SCK1)
/SD_CS: J5.2 (DAT3/CD), U1.9 (PA4)
/SD_MISO: J5.7 (DAT0), U1.11 (PA6_MISO1)
/SD_MOSI: J5.3 (CMD), U1.12 (PA7_MOSI1)
/TERM_PWR: D5.2 (A), J2.26
GND: J1.2, J2.1, J2.3, J2.5, J2.7, J2.9, J2.11, J2.13, J2.15, J2.17, J2.19, J2.20, J2.21, J2.22, J2.23, J2.24, J2.27, J2.28, J2.29, J2.30, J2.31, J2.33, J2.35, J2.37, J2.39, J2.41, J2.43, J2.45, J2.47, J2.49, J3.2, J4.2, J5.6 (VSS), J5.9 (SHIELD), JP1.2, U1.19 (GND), U1.20 (GND), U1.39 (GND)
unnamed: J3.1, R2.1
unnamed: J4.1, R1.1
unnamed: JP1.1, RN2.1 (common), RN4.1 (common)
unnamed: JP2.1, RN1.1 (common), RN3.1 (common)
VCC: D4.1 (K), D5.1 (K), JP2.2, R1.2, U1.38 (5V_USB)

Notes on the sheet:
SCSI 50 Pin Header
BluePill STM32
Micro SD Card
Mounting Hole
SCSI Termination Resistors
Power Input
